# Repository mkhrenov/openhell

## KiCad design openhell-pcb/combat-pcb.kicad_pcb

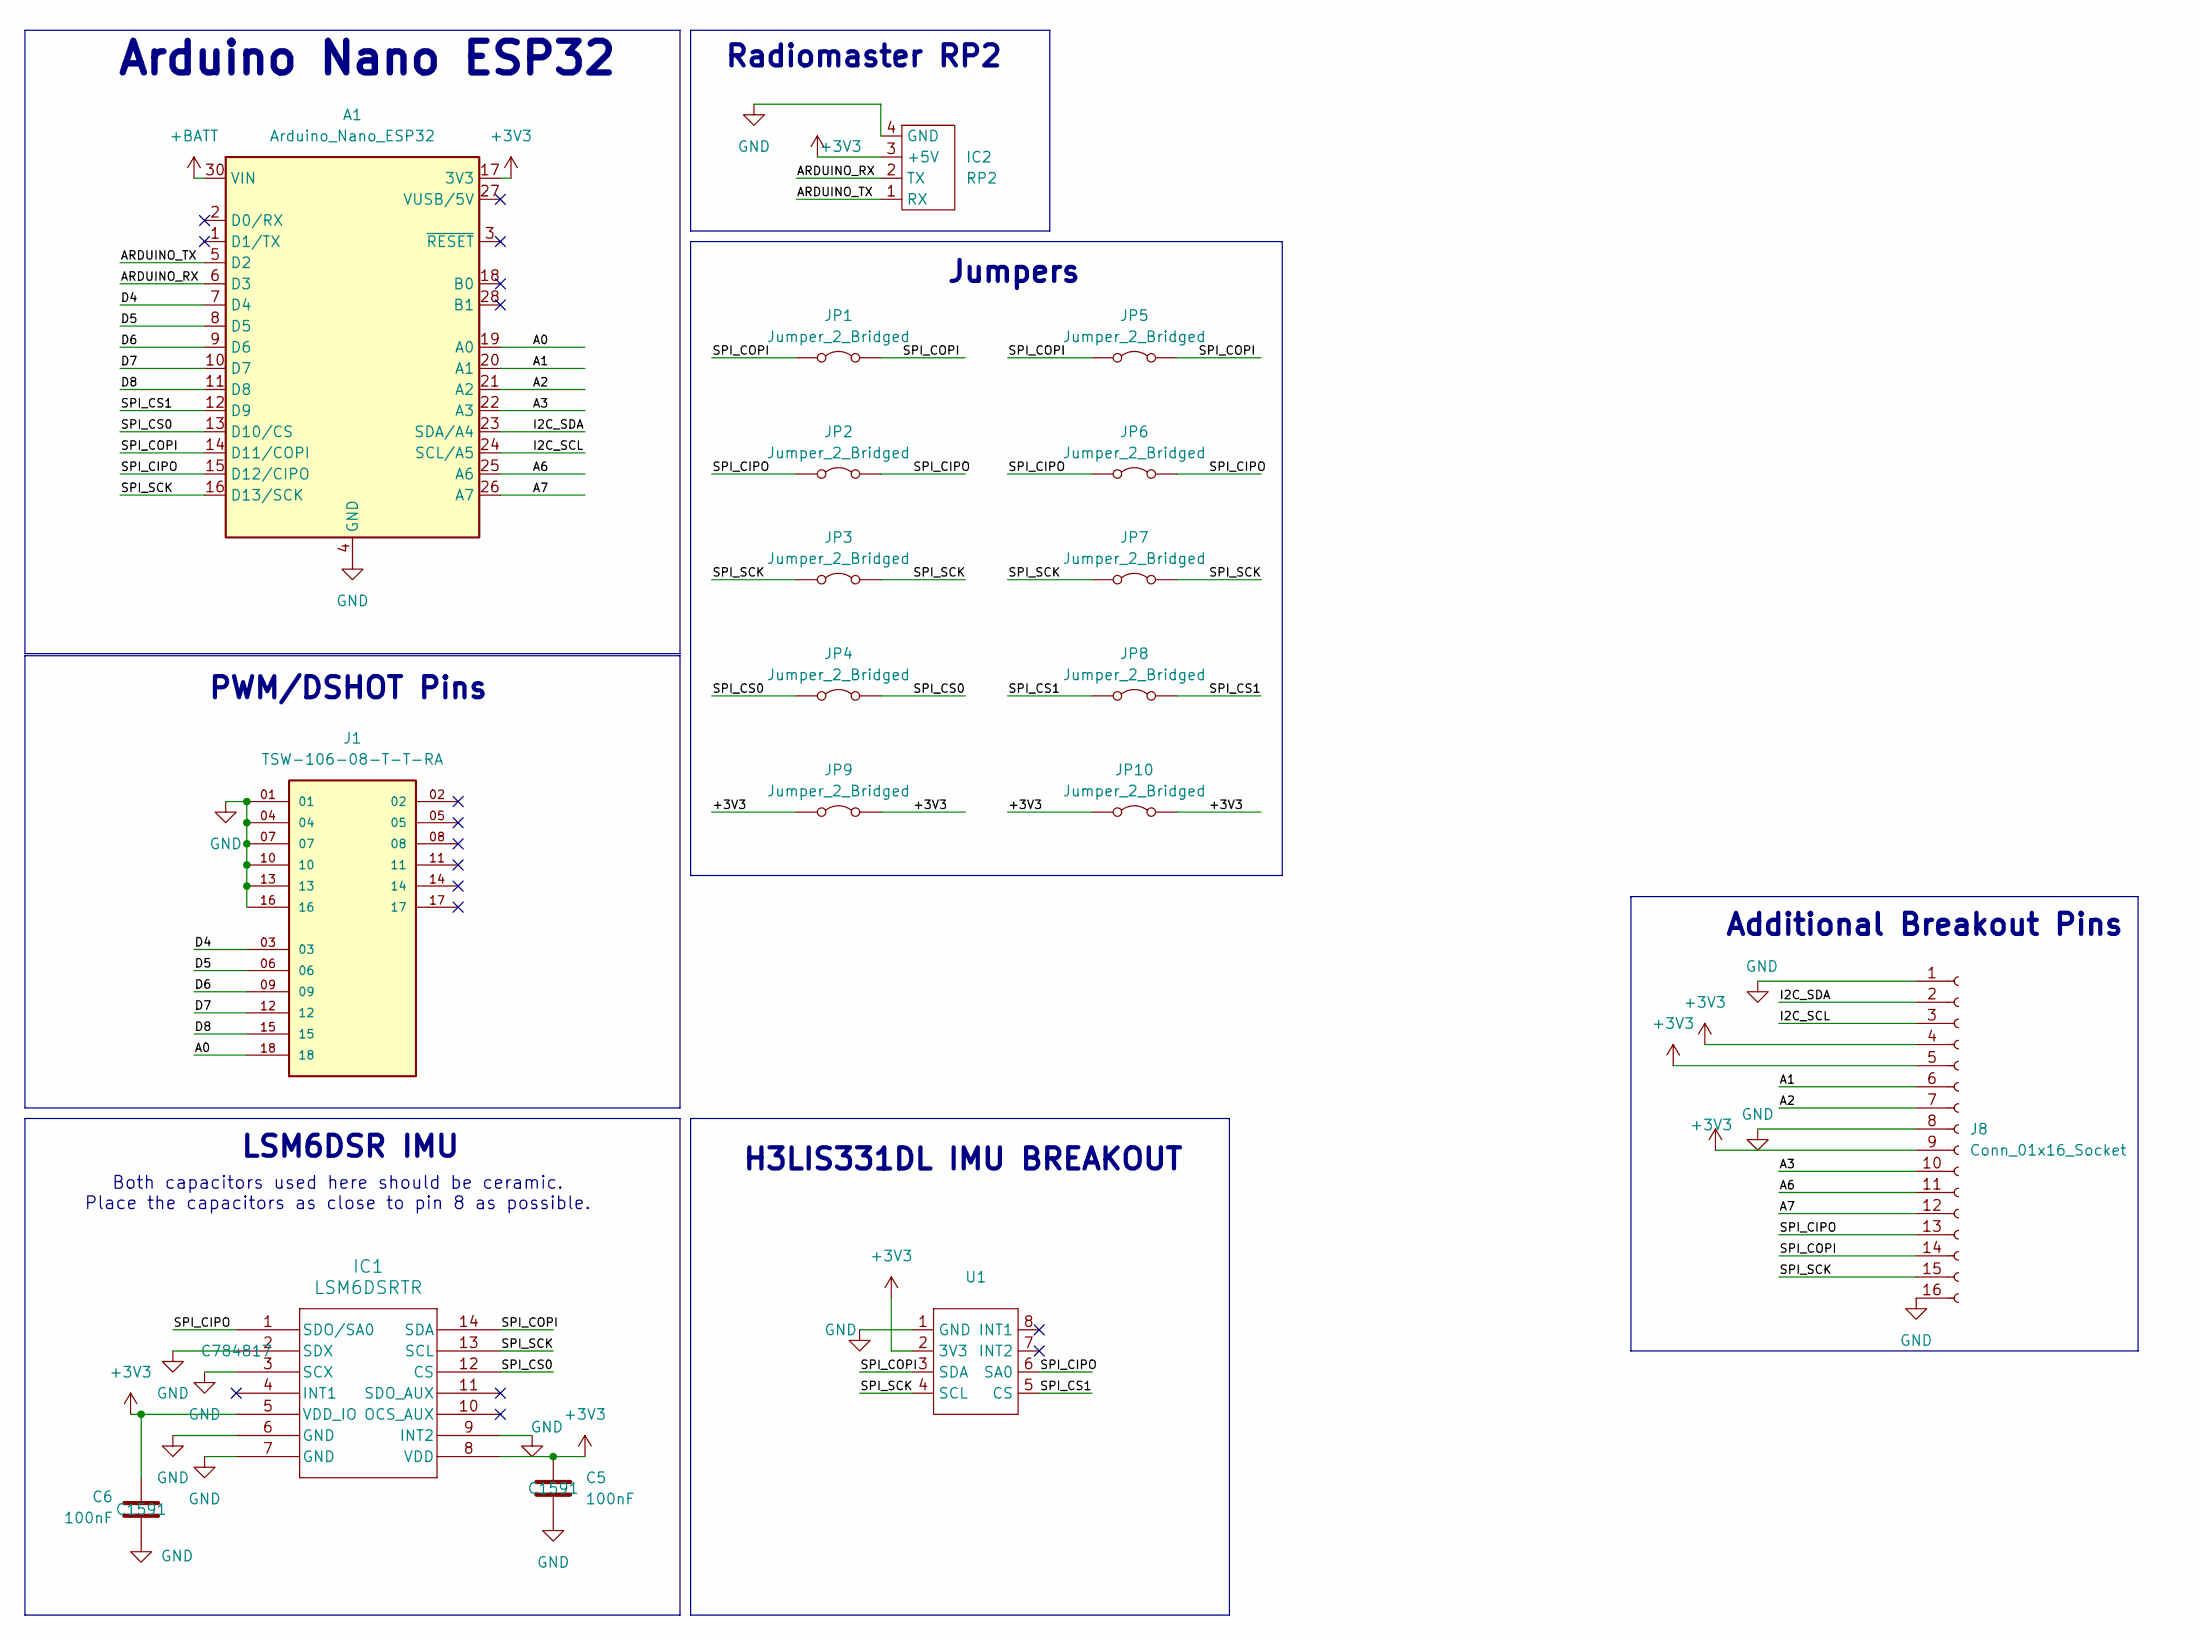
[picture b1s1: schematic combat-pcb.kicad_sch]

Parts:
A1: Arduino_Nano_ESP32; Arduino_Nano_ESP32_Tile
C5, C6: 100nF; C_0603_1608Metric; LCSC C1591
IC1: LSM6DSRTR; LGA-14_3x2.5mm_P0.5mm_LayoutBorder3x4y; LCSC C784817
IC2: RP2
J1: TSW-106-08-T-T-RA; SAMTEC_TSW-106-08-T-T-RA; PARTREV R
J8: Conn_01x16_Socket; PinSocket_1x16_P2.54mm_Vertical
JP1, JP2, JP3, JP4, JP5, JP6, JP7, JP8, JP9, JP10: Jumper_2_Bridged; SolderJumper-2_P1.3mm_Bridged_RoundedPad1.0x1.5mm
U1: H3LIS331DL-Breakout

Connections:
+3V3: A1.17 (3V3), C5.1, C6.1, IC1.5 (VDD_IO), IC1.8 (VDD), IC2.3 (+5V), J8.4, J8.5, J8.9, JP9.1 (A), JP9.2 (B), JP10.1 (A), JP10.2 (B), U1.2 (3V3)
+BATT: A1.30 (VIN); also elsewhere on the board
/A0: A1.19 (A0), J1.18
/A1: A1.20 (A1), J8.6
/A2: A1.21 (A2), J8.7
/A3: A1.22 (A3), J8.10
/A6: A1.25 (A6), J8.11
/A7: A1.26 (A7), J8.12
/ARDUINO_RX: A1.6 (D3), IC2.2 (TX)
/ARDUINO_TX: A1.5 (D2), IC2.1 (RX)
/D4: A1.7 (D4), J1.03
/D5: A1.8 (D5), J1.06
/D6: A1.9 (D6), J1.09
/D7: A1.10 (D7), J1.12
/D8: A1.11 (D8), J1.15
/I2C_SCL: A1.24 (SCL/A5), J8.3
/I2C_SDA: A1.23 (SDA/A4), J8.2
/SPI_CIPO: A1.15 (D12/CIPO), IC1.1 (SDO/SA0), J8.13, JP2.1 (A), JP2.2 (B), JP6.1 (A), JP6.2 (B), U1.6 (SA0)
/SPI_COPI: A1.14 (D11/COPI), IC1.14 (SDA), J8.14, JP1.1 (A), JP1.2 (B), JP5.1 (A), JP5.2 (B), U1.3 (SDA)
/SPI_CS0: A1.13 (D10/CS), IC1.12 (CS), JP4.1 (A), JP4.2 (B)
/SPI_CS1: A1.12 (D9), JP8.1 (A), JP8.2 (B), U1.5 (CS)
/SPI_SCK: A1.16 (D13/SCK), IC1.13 (SCL), J8.15, JP3.1 (A), JP3.2 (B), JP7.1 (A), JP7.2 (B), U1.4 (SCL)
GND: A1.4 (GND), A1.29 (GND), C5.2, C6.2, IC1.2 (SDX), IC1.3 (SCX), IC1.6 (GND), IC1.7 (GND), IC1.9 (INT2), IC2.4 (GND), J1.01, J1.04, J1.07, J1.10, J1.13, J1.16, J8.1, J8.8, J8.16, U1.1 (GND); also elsewhere on the board

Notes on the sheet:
Both capacitors used here should be ceramic. Place the capacitors as close to pin 8 as possible.
Jumpers
PWM/DSHOT Pins
H3LIS331DL IMU BREAKOUT
Additional Breakout Pins
LSM6DSR IMU
Arduino Nano ESP32
Radiomaster RP2

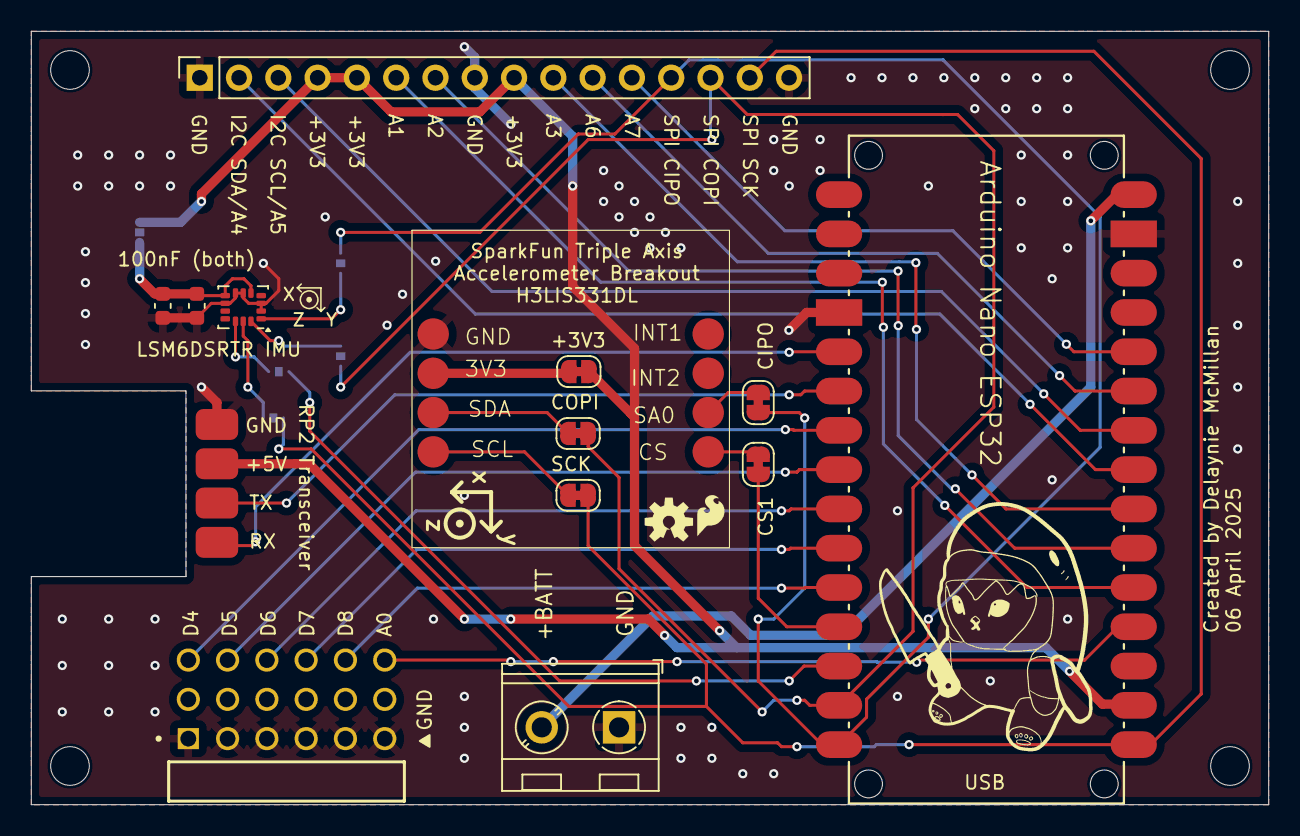
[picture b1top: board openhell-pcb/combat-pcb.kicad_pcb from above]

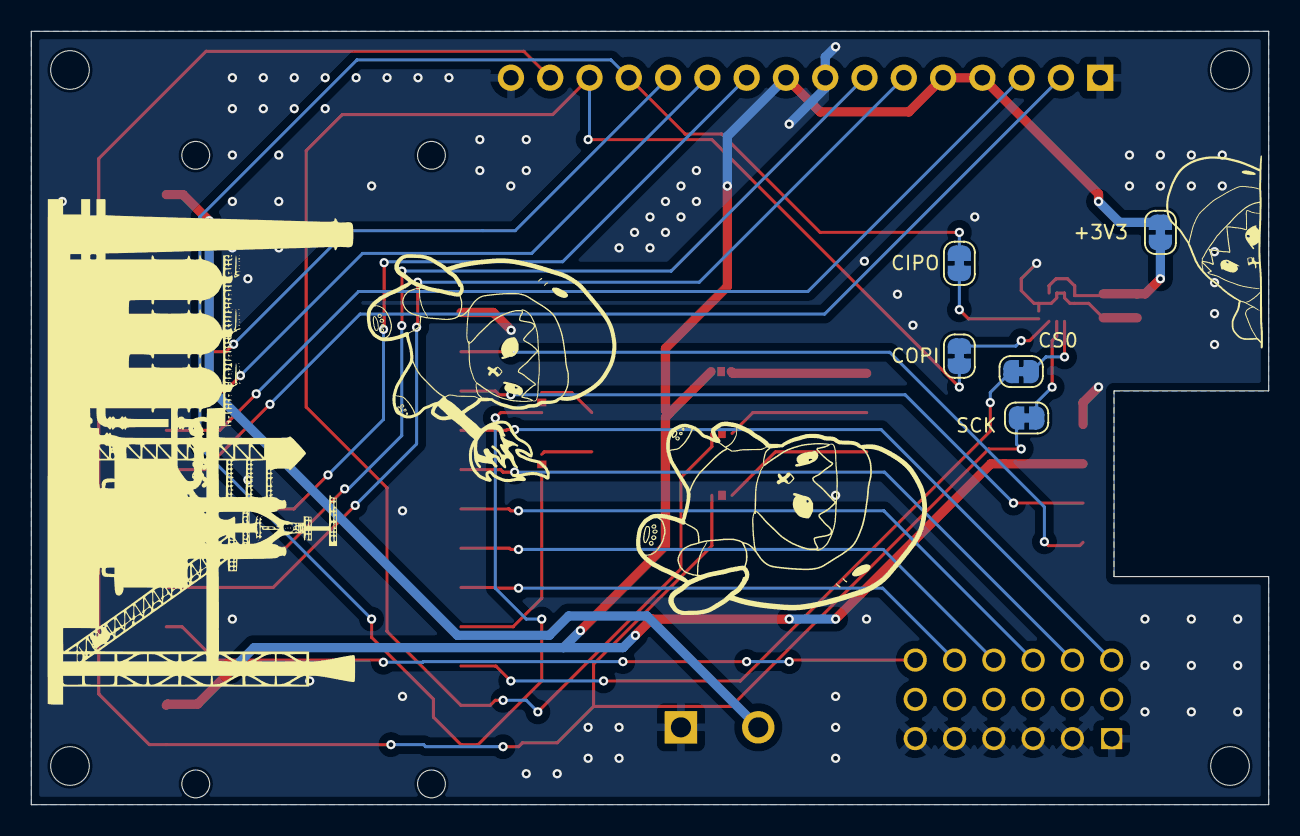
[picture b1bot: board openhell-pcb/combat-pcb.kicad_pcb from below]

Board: 2 copper layers, 80.0 x 50.0 mm, 19 parts (5 on the bottom side), 23 nets.

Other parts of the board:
J7: Screw_Terminal_01x02; TerminalBlock_RND_205-00045_1x02_P5.00mm_Horizontal

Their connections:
+BATT: J7.2; also elsewhere on the board
GND: J7.1; also elsewhere on the board

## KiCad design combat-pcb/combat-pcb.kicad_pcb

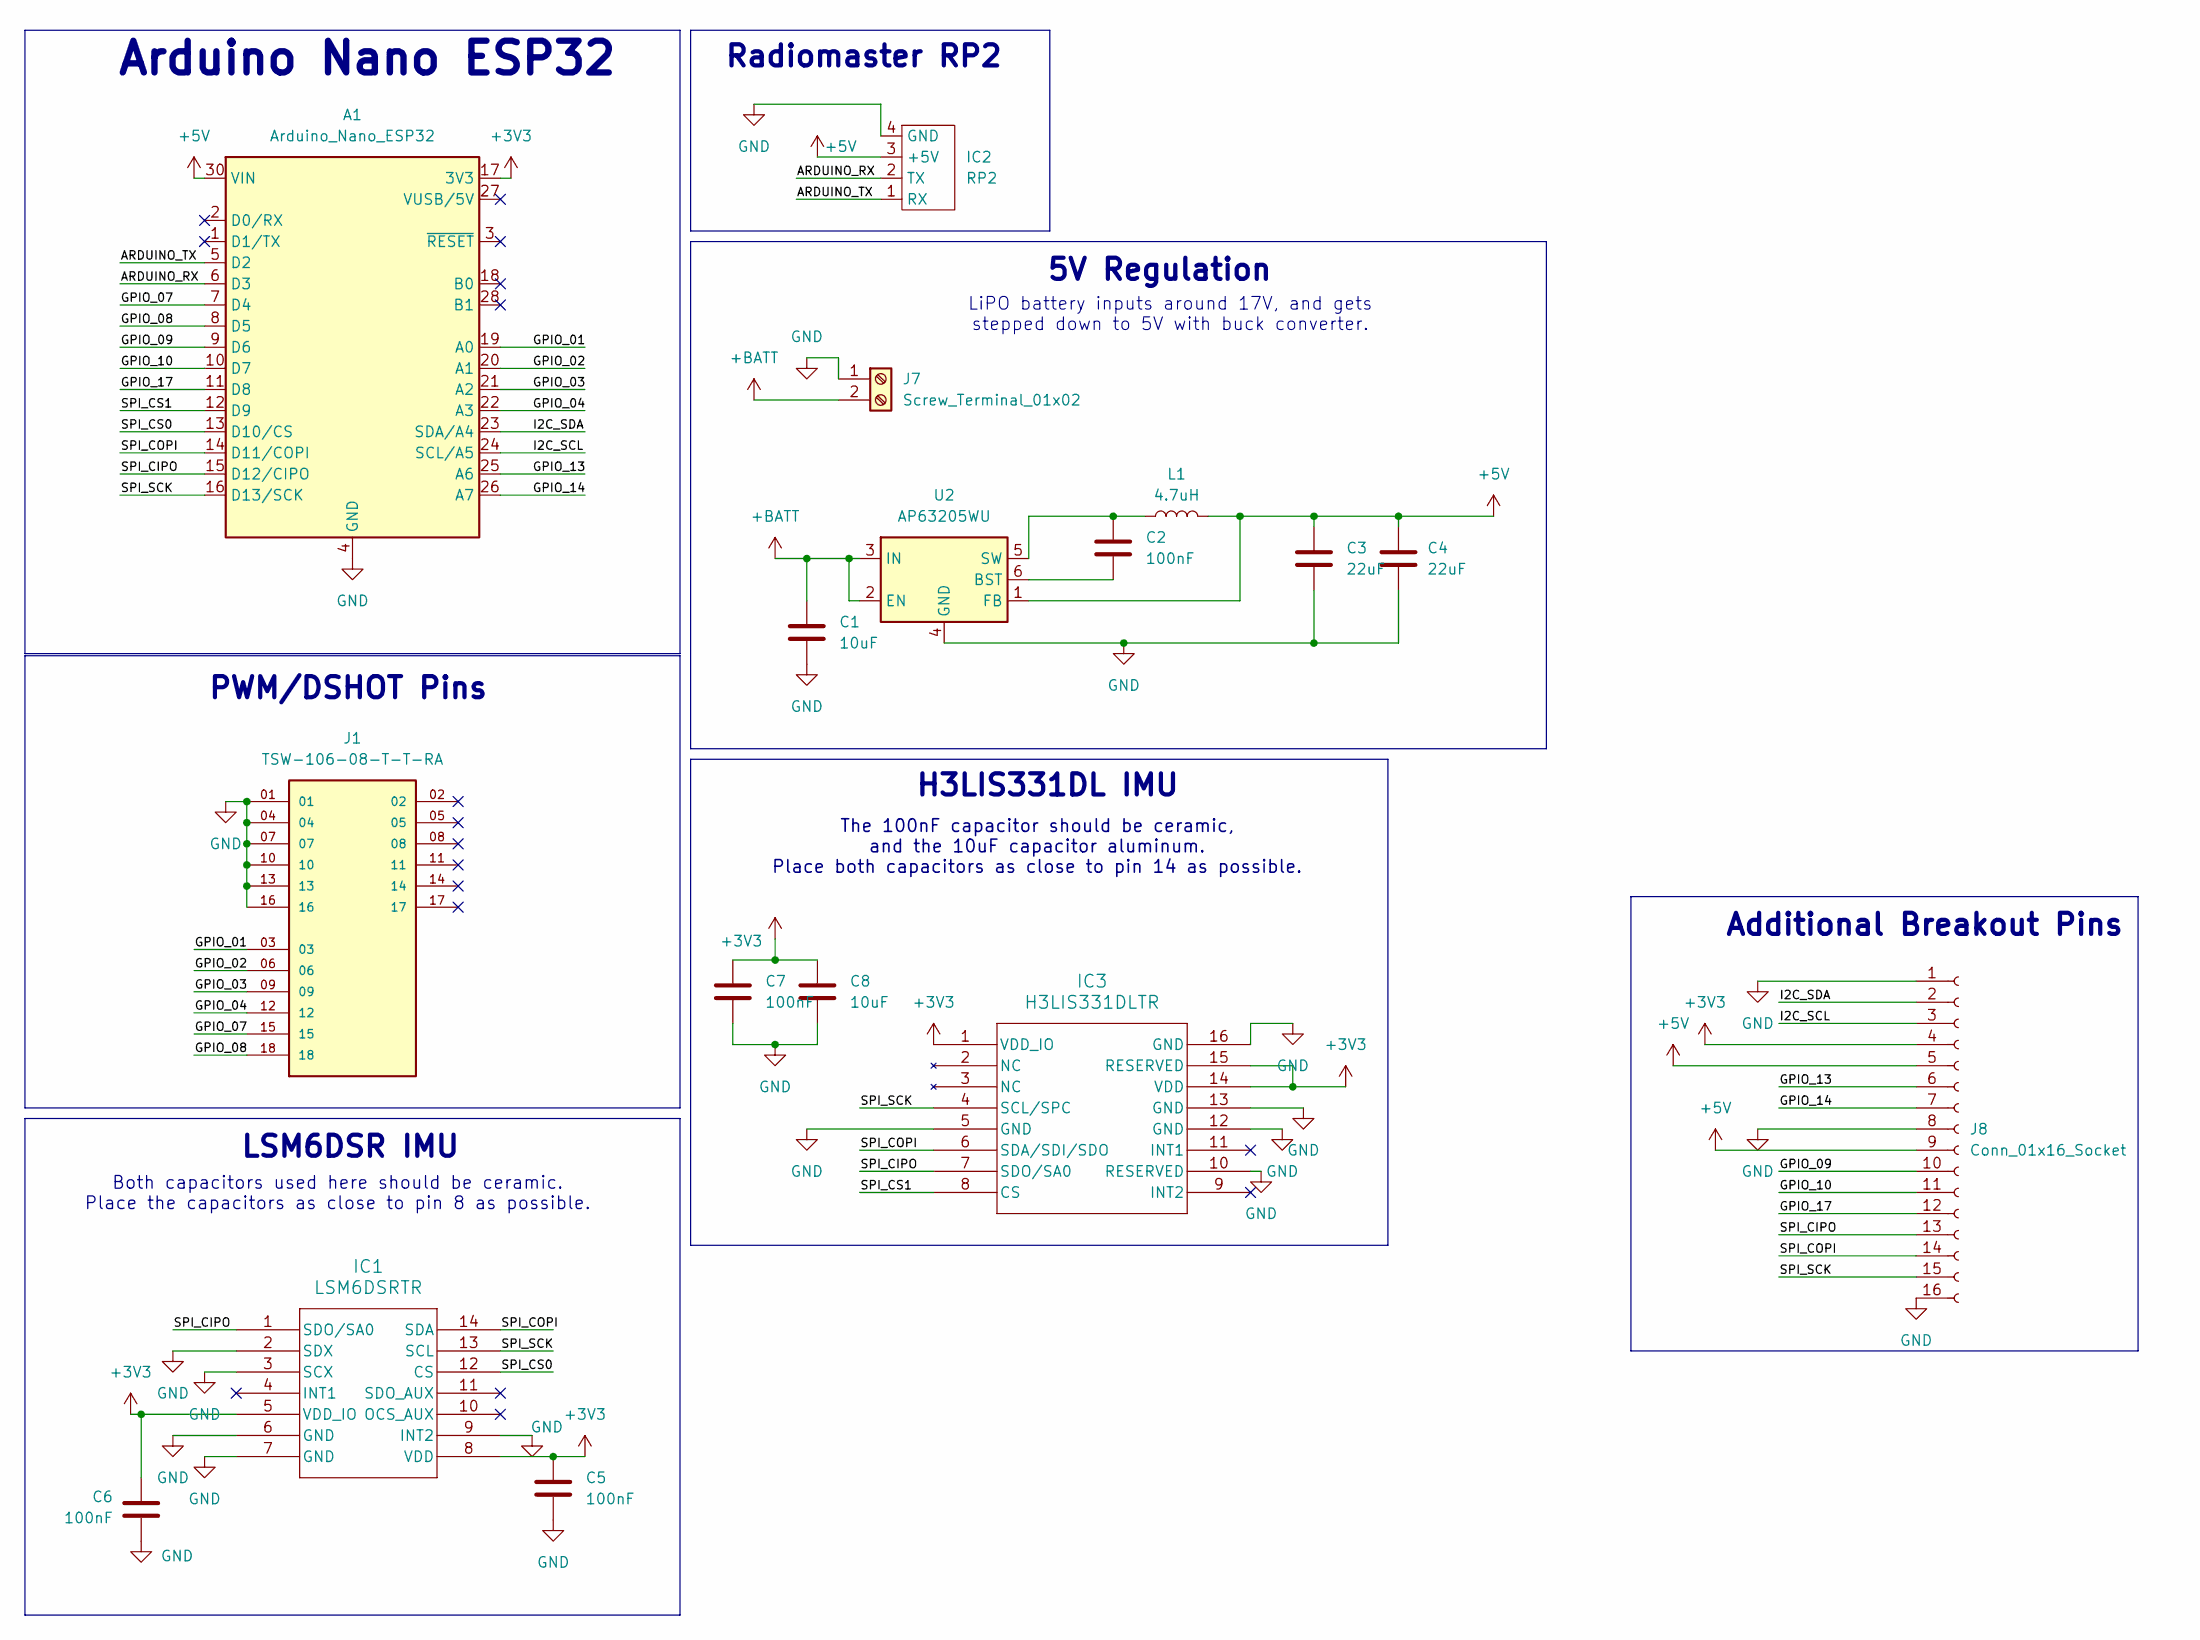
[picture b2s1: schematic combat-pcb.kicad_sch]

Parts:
A1: Arduino_Nano_ESP32; Arduino_Nano_ESP32_Tile
C1: 10uF; C_0603_1608Metric
C2: 100nF; C_0603_1608Metric
C3, C4: 22uF; C_0603_1608Metric
C5, C6, C7: 100nF; C_0402_1005Metric
C8: 10uF; C_0805_2012Metric
IC1: LSM6DSRTR; LGA-14L_2P5X3X0P83_STM
IC2: RP2
IC3: H3LIS331DLTR; QFN_31DLTR_STM
J1: TSW-106-08-T-T-RA; SAMTEC_TSW-106-08-T-T-RA; PARTREV R
J7: Screw_Terminal_01x02; TerminalBlock_RND_205-00045_1x02_P5.00mm_Horizontal
J8: Conn_01x16_Socket; PinSocket_1x16_P2.54mm_Vertical
L1: 4.7uH; IND_ASPI-4030S-4R7M-T
U2: AP63205WU; TSOT-23-6

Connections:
+3V3: A1.17 (3V3), C5.1, C6.1, C7.1, C8.1, IC1.5 (VDD_IO), IC1.8 (VDD), IC3.1 (VDD_IO), IC3.14 (VDD), IC3.15 (RESERVED), J8.4
+5V: A1.30 (VIN), C3.1, C4.1, IC2.3 (+5V), J8.5, J8.9, L1.2, U2.1 (FB)
+BATT: C1.1, J7.2, U2.2 (EN), U2.3 (IN)
/ARDUINO_RX: A1.6 (D3), IC2.2 (TX)
/ARDUINO_TX: A1.5 (D2), IC2.1 (RX)
/GPIO_01: A1.19 (A0), J1.03
/GPIO_02: A1.20 (A1), J1.06
/GPIO_03: A1.21 (A2), J1.09
/GPIO_04: A1.22 (A3), J1.12
/GPIO_07: A1.7 (D4), J1.15
/GPIO_08: A1.8 (D5), J1.18
/GPIO_09: A1.9 (D6), J8.10
/GPIO_10: A1.10 (D7), J8.11
/GPIO_13: A1.25 (A6), J8.6
/GPIO_14: A1.26 (A7), J8.7
/GPIO_17: A1.11 (D8), J8.12
/I2C_SCL: A1.24 (SCL/A5), J8.3
/I2C_SDA: A1.23 (SDA/A4), J8.2
/SPI_CIPO: A1.15 (D12/CIPO), IC1.1 (SDO/SA0), IC3.7 (SDO/SA0), J8.13
/SPI_COPI: A1.14 (D11/COPI), IC1.14 (SDA), IC3.6 (SDA/SDI/SDO), J8.14
/SPI_CS0: A1.13 (D10/CS), IC1.12 (CS)
/SPI_CS1: A1.12 (D9), IC3.8 (CS)
/SPI_SCK: A1.16 (D13/SCK), IC1.13 (SCL), IC3.4 (SCL/SPC), J8.15
GND: A1.4 (GND), A1.29 (GND), C1.2, C3.2, C4.2, C5.2, C6.2, C7.2, C8.2, IC1.2 (SDX), IC1.3 (SCX), IC1.6 (GND), IC1.7 (GND), IC1.9 (INT2), IC2.4 (GND), IC3.5 (GND), IC3.10 (RESERVED), IC3.12 (GND), IC3.13 (GND), IC3.16 (GND), J1.01, J1.04, J1.07, J1.10, J1.13, J1.16, J7.1, J8.1, J8.8, J8.16, U2.4 (GND)
unnamed: C2.2, U2.6 (BST)
unnamed: C2.1, L1.1, U2.5 (SW)

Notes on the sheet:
Both capacitors used here should be ceramic. Place the capacitors as close to pin 8 as possible.
PWM/DSHOT Pins
H3LIS331DL IMU
The 100nF capacitor should be ceramic, and the 10uF capacitor aluminum. Place both capacitors as close to pin 14 as possible.
LiPO battery inputs around 17V, and gets stepped down to 5V with buck converter.
Additional Breakout Pins
LSM6DSR IMU
Arduino Nano ESP32
5V Regulation
Radiomaster RP2

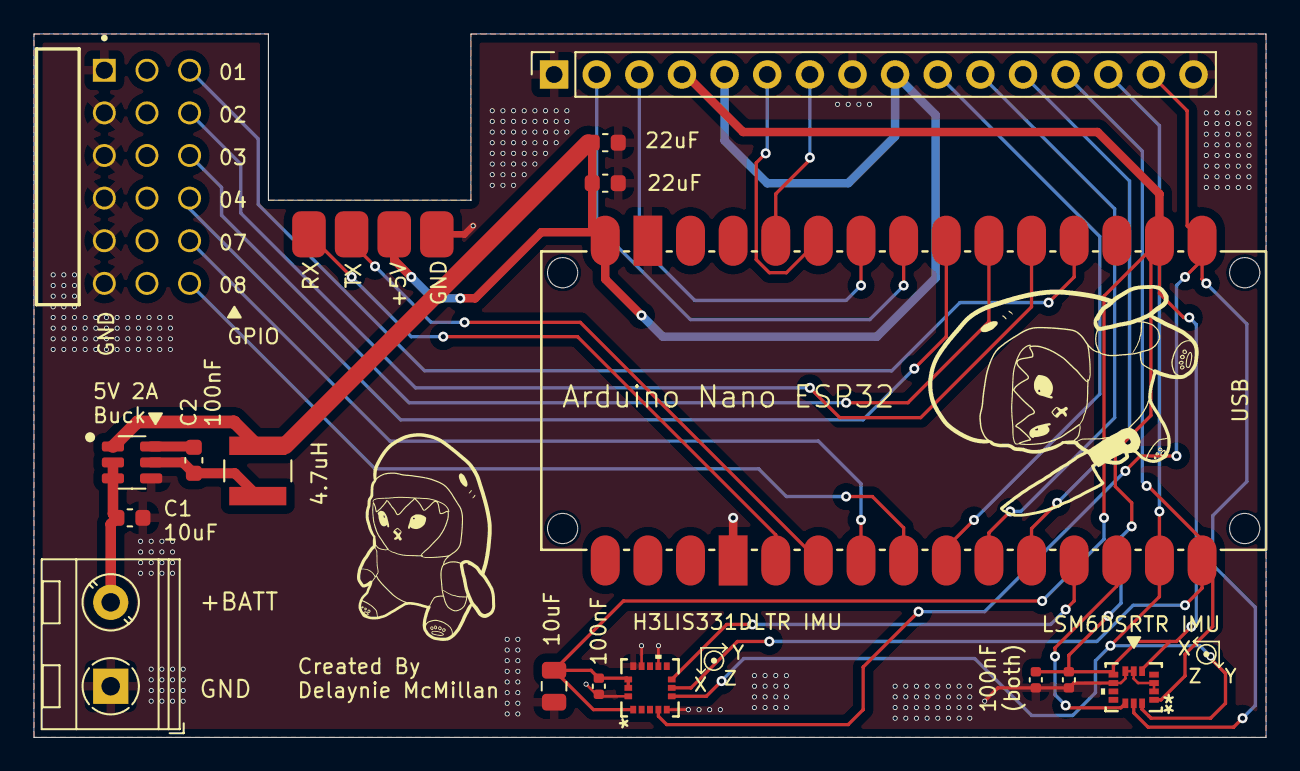
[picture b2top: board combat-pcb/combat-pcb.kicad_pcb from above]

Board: 2 copper layers, 73.4 x 41.9 mm, 17 parts (0 on the bottom side), 26 nets.

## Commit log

2025-02-18 starting CAD
2025-03-02 Pancake
2025-03-02 Hat v1
2025-03-02 gitignore
2025-03-03 Added lift EDF
2025-03-03 Updated EDF with 40mm config
2025-03-04 reworking to hovermelt
2025-03-04 fasteners and fans
2025-03-04 reorganization to flatter hierarchy, removed unneeded parts
2025-03-08 brim, etc
2025-03-08 renaming
2025-03-08 Moved spreader file
2025-03-08 Boilerplate for firmware with platformIO
2025-03-09 Electronics, weight
2025-03-10 added combat pcb files
    version 0, pre-design review
2025-03-12 placed JLCPCB order. these are the files I sent
2025-03-29 Updated EDFs and EDF mounting positions
2025-03-29 Added mounting for diffuser
2025-04-01 small updates to spreader and 3D prints
2025-04-04 Updating hat to improve fitment
2025-04-04 Updated Hat with Protoboard Geometry
2025-04-08 V2 of OPENHELL
2025-04-08 added LED channel
2025-04-08 Sensors work, CRSF works
2025-04-08 Load cell and blade files
2025-04-10 Basic working stuff
2025-04-11 EDF characterization
2025-04-11 Updated to 2nd order model
2025-04-12 Updated plots
2025-04-12 Updated channels to put arming on Ch5, messing with rotation setpoints
2025-04-12 Updated thrust constant, fixed RMT channel re-use conflict with LEDs and motors, temporarily disabled PI controller for angular rate
2025-04-13 Electrical analysis + weapon 'locks'
2025-04-13 Added gap in center weapon lock
2025-04-14 Updated hat w/ more electronics space
2025-04-19 Moved over to LSM6DSR for low-g IMU, own drivers
2025-04-19 Fixed angular velocity axis definition, added RPM telemetry
2025-04-19 Comments to remember which GPIOs map to which pins
2025-04-19 Comments to remember which GPIO pins correspond to which Arduino pin numbers
2025-04-20 Added linear ramp on thrust cyclic amplitude rather than cutting to 0 (hopefully to deal with voltage spike events)
2025-04-20 Fusing two imus, linear fade-in
2025-04-21 Hovermelting works, added bias calibration, and currently use volatile "rescale" variable to calibrate low-g imu, high-g imu temporarily disabled, need non-volatile storage and better calibration.
2025-04-28 Added non-volatile storage for gyro scale factors, re-ordered input channels, rescaled
2025-04-29 New weapon lock + service cap + deeper plastite holes
2025-04-30 Removed amplitude constraint, enabled independent tuning, made "turning" (dphi) do something
2025-05-05 pcb updated to design used in May 2025 comp
    do note that the pcb file here includes the 5V power line connection
    that was missing on the actual pcb that got used.
    renamed combat-pcb to openhell-pcb.
